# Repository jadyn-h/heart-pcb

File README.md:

# heart-pcb
I made this project with Hack Club guides from Sleepover and Stasis. This is a heart shaped PCB that has red blinking LEDs. I designed it using KiCad.
I made the project because I wanted to learn how a circut board works and what the process of creating one requires. This is my first hardware project and I wanted to create something that was visually interesting (flashing lights are pretty cool). 
My process was recorded on Lapse.

[Heart PCB-bom.csv](https://github.com/user-attachments/files/26512488/Heart.PCB-bom.csv)
Name                                Purpose            Quantity   Total Cost (USD)                     Link                                    Distributor
"PCB prototype:Y2-12297275A"   "Printing the PCB"         5            13.10            "https://cart.jlcpcb.com/shopcart/cart/"                "JLCPCB"

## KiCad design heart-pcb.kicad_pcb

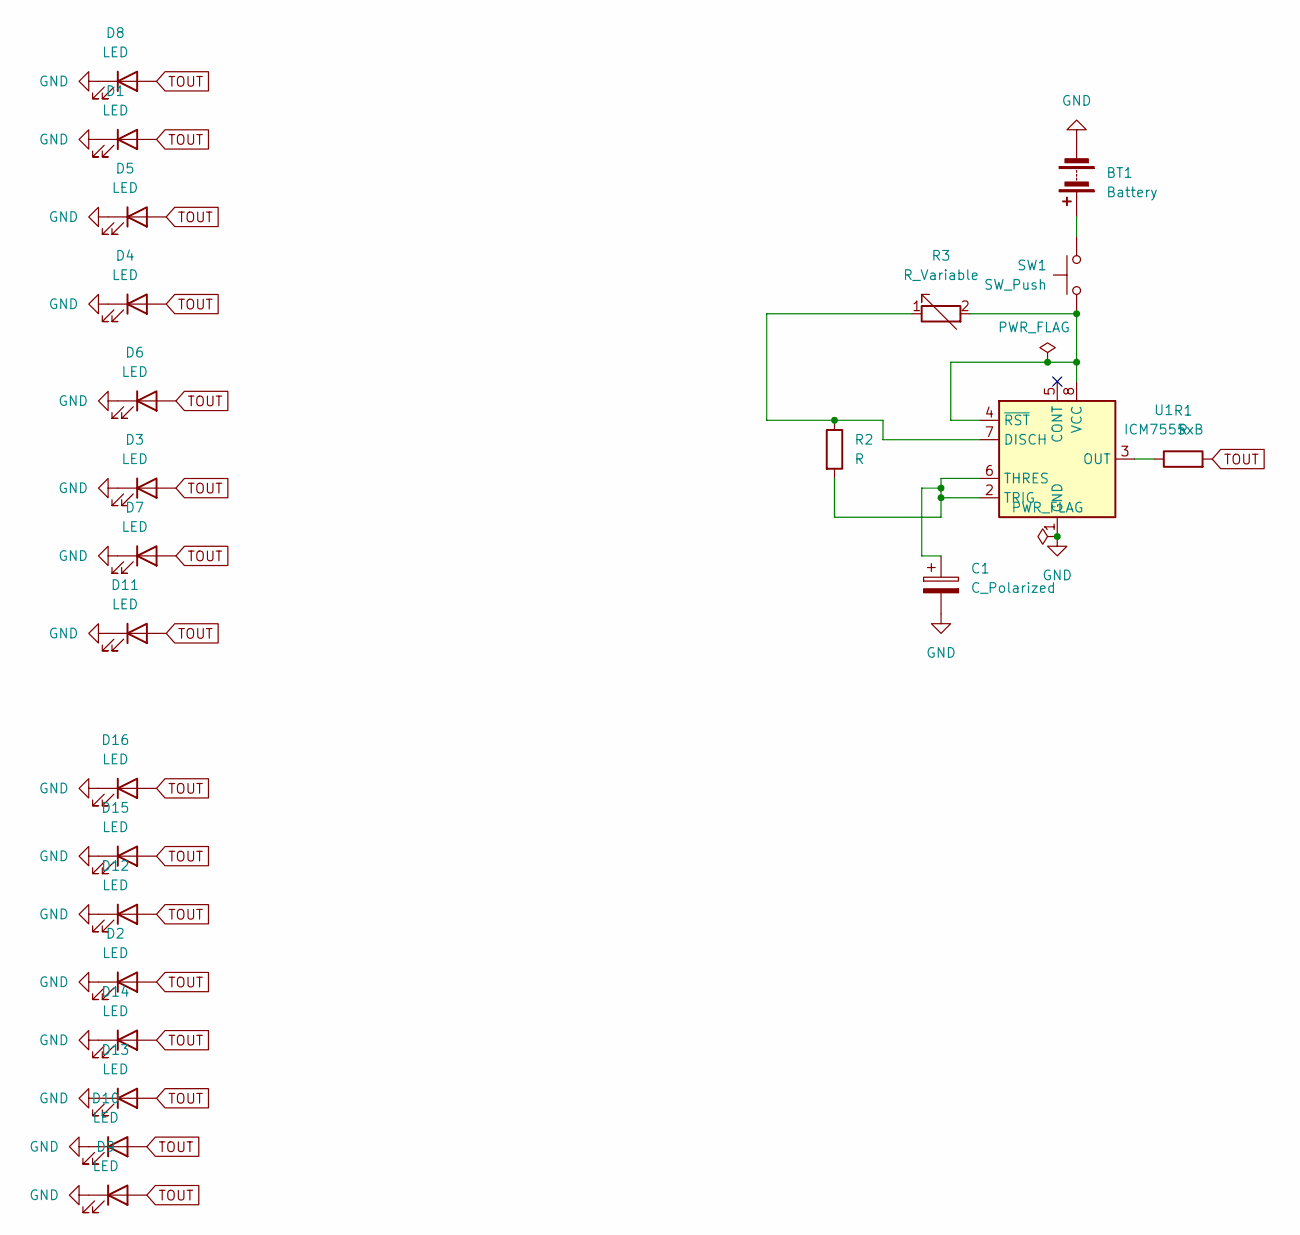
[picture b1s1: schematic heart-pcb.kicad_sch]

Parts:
BT1: Battery; SolderWire-0.1sqmm_1x02_P3.6mm_D0.4mm_OD1mm
C1: C_Polarized; CP_Radial_D5.0mm_P2.50mm
D1, D2, D3, D4, D5, D6, D7, D8, D9, D10, D11, D12, D13, D14, D15, D16: LED; LED_D5.0mm
R1, R2: R; R_Axial_DIN0207_L6.3mm_D2.5mm_P7.62mm_Horizontal
R3: R_Variable; Potentiometer_Bourns_3386P_Vertical
SW1: SW_Push; SW_PUSH_6mm
U1: ICM7555xB; SOIC-8_3.9x4.9mm_P1.27mm

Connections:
GND: BT1.2 (-), C1.2, D1.1 (K), D2.1 (K), D3.1 (K), D4.1 (K), D5.1 (K), D6.1 (K), D7.1 (K), D8.1 (K), D9.1 (K), D10.1 (K), D11.1 (K), D12.1 (K), D13.1 (K), D14.1 (K), D15.1 (K), D16.1 (K), U1.1 (GND)
unnamed: BT1.1 (+), SW1.1
unnamed: R2.1, R3.1, U1.7 (DISCH)
unnamed: R1.1, U1.3 (OUT)
unnamed: C1.1, R2.2, U1.2 (TRIG), U1.6 (THRES)
unnamed: R3.2, SW1.2, U1.4 (~RST), U1.8 (VCC)
TOUT: D1.2 (A), D2.2 (A), D3.2 (A), D4.2 (A), D5.2 (A), D6.2 (A), D7.2 (A), D8.2 (A), D9.2 (A), D10.2 (A), D11.2 (A), D12.2 (A), D13.2 (A), D14.2 (A), D15.2 (A), D16.2 (A), R1.2

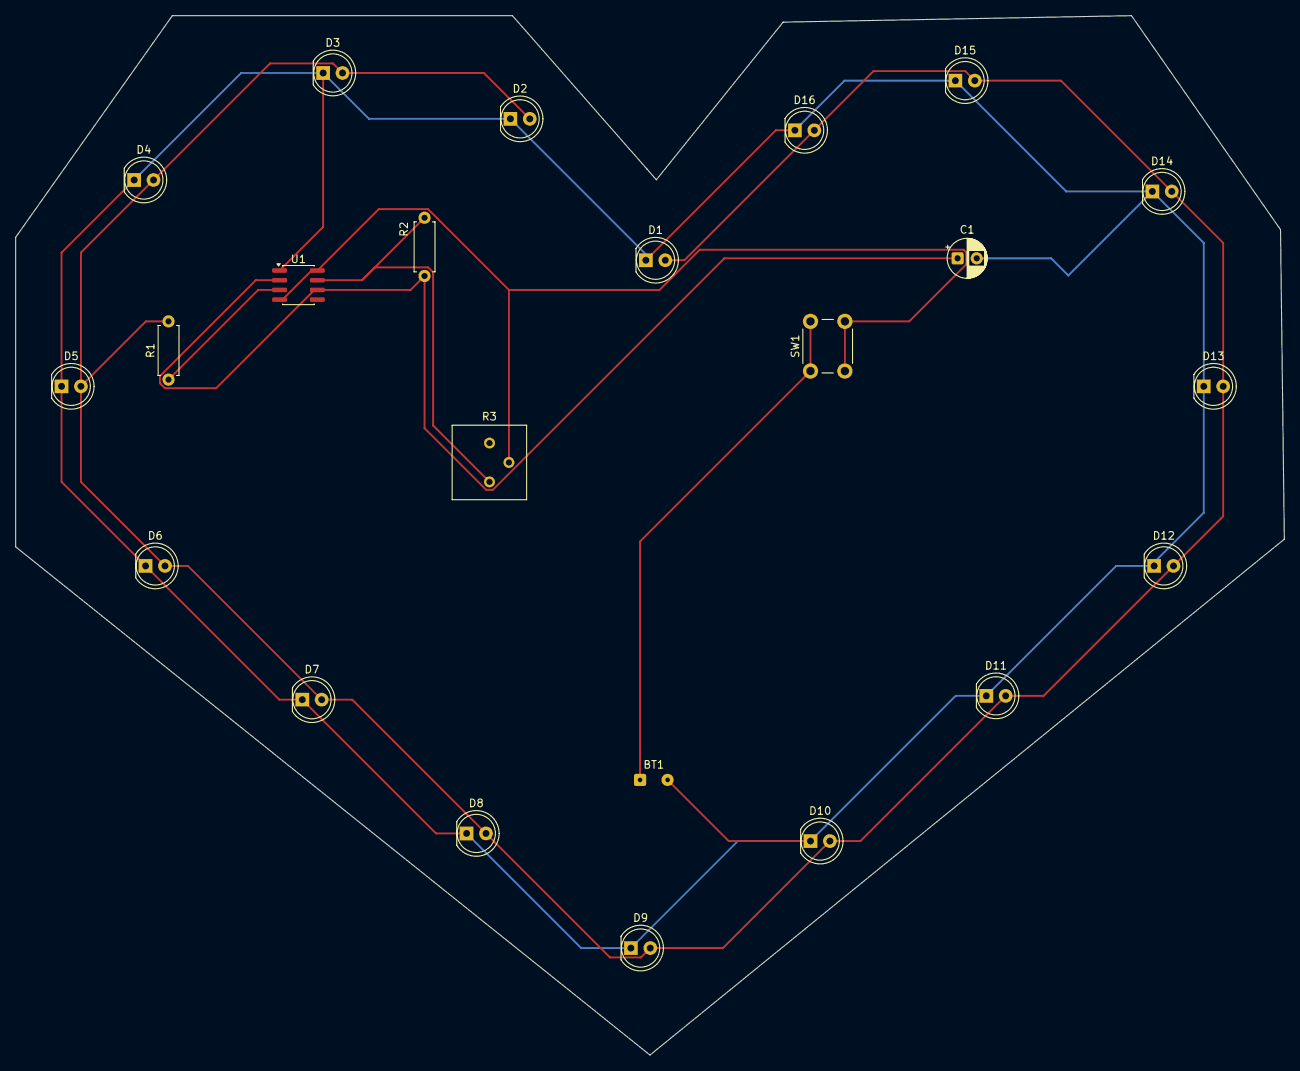
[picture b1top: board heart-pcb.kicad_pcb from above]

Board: 2 copper layers, 166.0 x 136.0 mm, 23 parts (0 on the bottom side), 7 nets.

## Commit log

2026-04-06 added journal from Stasis
2026-04-06 Update README.md w/ pictures
